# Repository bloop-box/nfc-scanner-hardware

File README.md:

# Bloop NFC Scanner Hardware

[Documentation](https://bloop-box.github.io/nfc-scanner-hardware)

Connect an RC522 based NFC-Reader to your computer using USB

The project is based around a Raspberry Pi [RP2040](https://www.raspberrypi.com/documentation/microcontrollers/rp2040.html) microcontroller. It would have been possible to solve this with a much simpler controller but availability and pricing at the time of development as well as ease of use made the RP2040 with built in USB the best choice. 

The board is designed using KiCAD 6 with production and assembly by JLCPCB in mind. All parts are selected to be available from JLCPCB at the time of writing and as many parts as possible are used from their basic library.

## Case
A simple case design can be found in the case subfolder. It fits when the two boards are connected with standard angled 2.54mm pitch connectors as seen in the picture. 

The two halves can be connected with self-tapping, countersunk M3x6 screws

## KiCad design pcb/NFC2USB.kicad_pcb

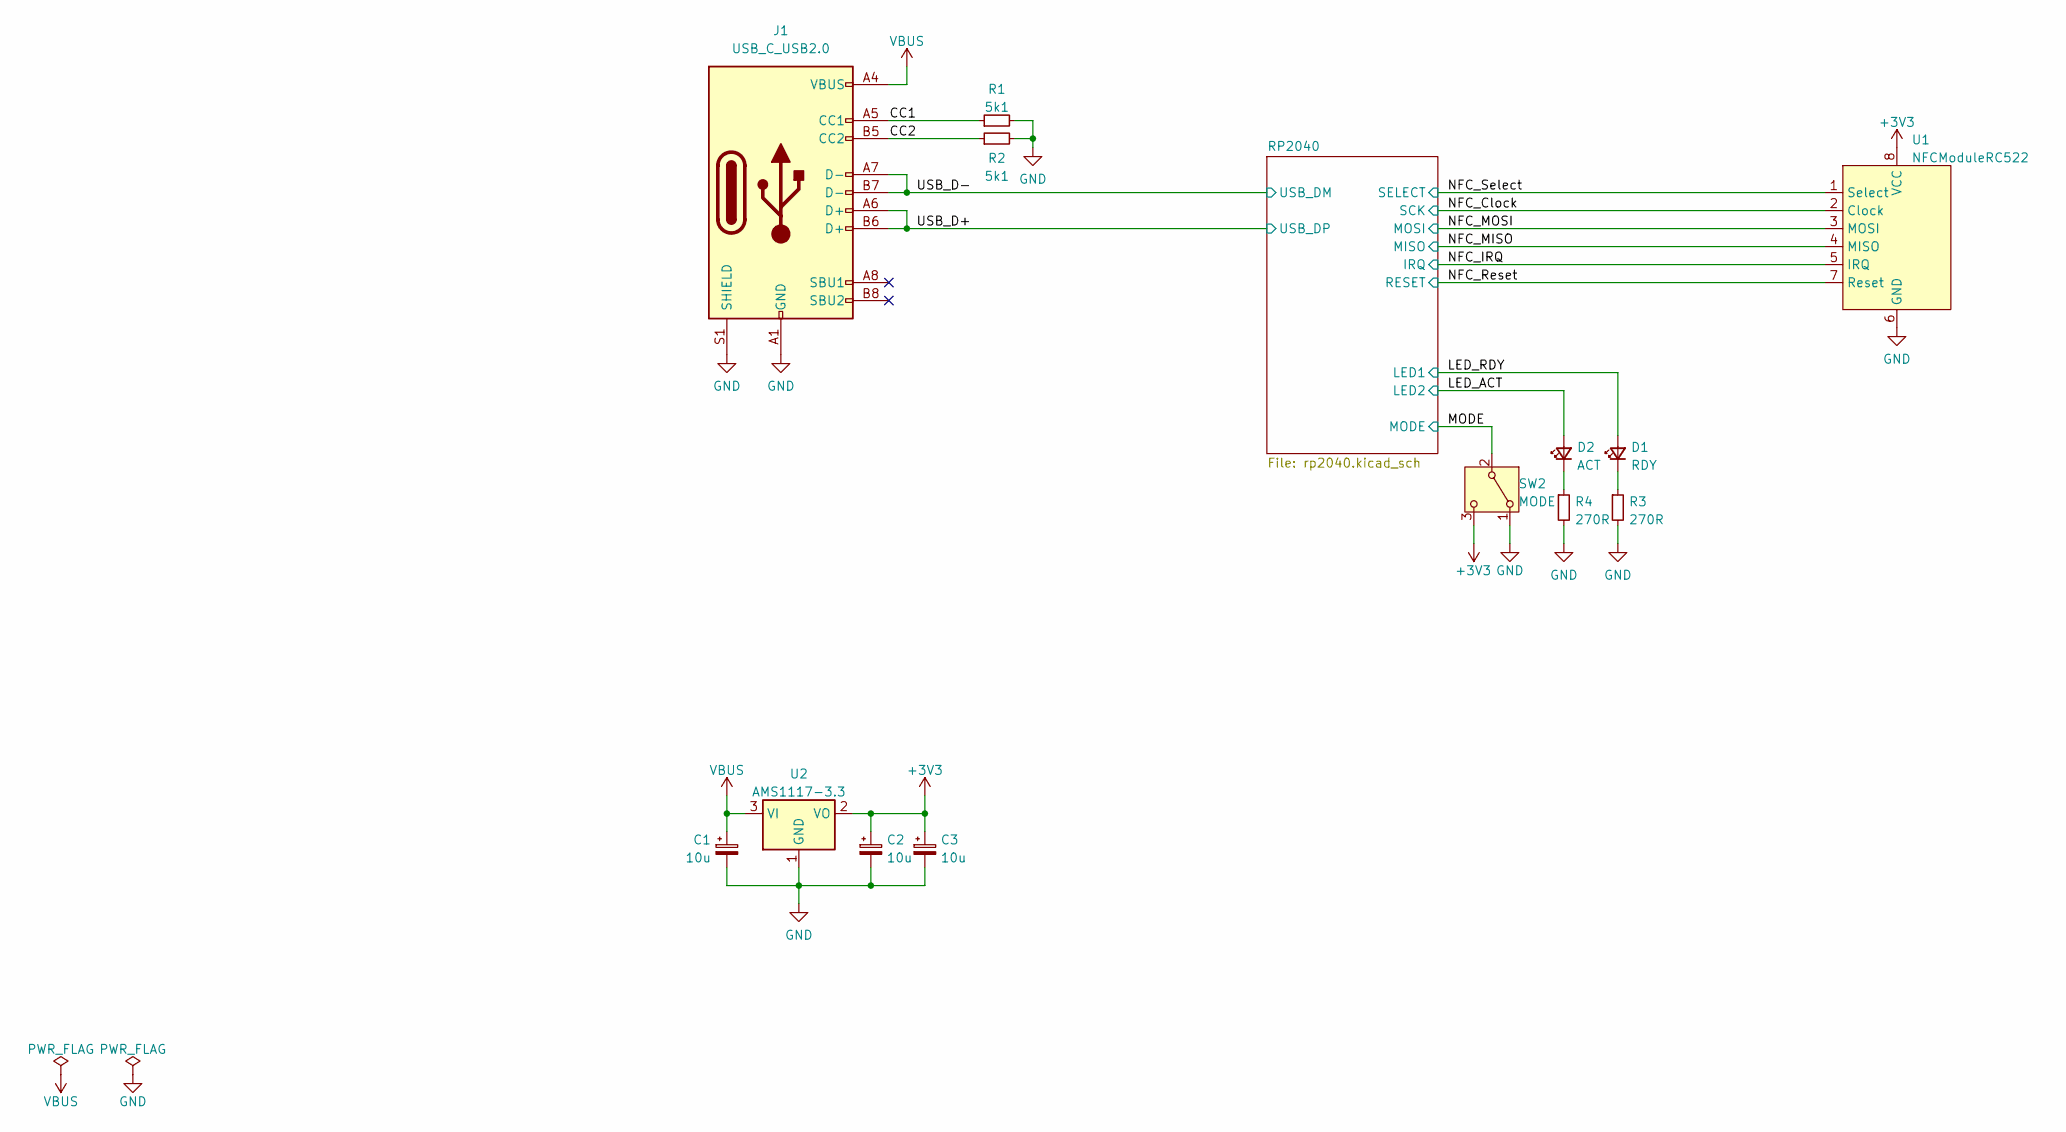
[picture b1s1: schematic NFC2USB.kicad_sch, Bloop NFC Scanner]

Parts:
C1, C2, C3: 10u; CP_EIA-3216-18_Kemet-A; LCSC C7171
D1: RDY; LED_0603_1608Metric; LCSC C72038
D2: ACT; LED_0603_1608Metric; LCSC C72043
J1: USB_C_USB2.0; USB_C_Receptacle_HRO_TYPE-C-31-M-12; LCSC C2894897
R1, R2: 5k1; R_0402_1005Metric; LCSC C25905
R3, R4: 270R; R_0603_1608Metric; LCSC C22966
SW2: MODE; SW_SPDT_PCM12; LCSC C431541
U1: NFCModuleRC522; PinSocket_1x08_P2.54mm_Vertical; LCSC C2897390
U2: AMS1117-3.3; SOT-223-3_TabPin2; LCSC C6186

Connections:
+3V3: C2.1, C3.1, SW2.3 (C), U1.8 (VCC), U2.2 (VO); also elsewhere on the board
/CC1: J1.A5 (CC1), R1.1
/CC2: J1.B5 (CC2), R2.1
/LED_ACT: D2.2 (A); also elsewhere on the board
/LED_RDY: D1.2 (A); also elsewhere on the board
/MODE: SW2.2 (B); also elsewhere on the board
/NFC_Clock: U1.2 (Clock); also elsewhere on the board
/NFC_IRQ: U1.5 (IRQ); also elsewhere on the board
/NFC_MISO: U1.4 (MISO); also elsewhere on the board
/NFC_MOSI: U1.3 (MOSI); also elsewhere on the board
/NFC_Reset: U1.7 (Reset); also elsewhere on the board
/NFC_Select: U1.1 (Select); also elsewhere on the board
/USB_D+: J1.A6 (D+), J1.B6 (D+); also elsewhere on the board
/USB_D-: J1.A7 (D-), J1.B7 (D-); also elsewhere on the board
GND: C1.2, C2.2, C3.2, J1.A1 (GND), J1.A12 (GND), J1.B1 (GND), J1.B12 (GND), J1.S1 (SHIELD), R1.2, R2.2, R3.2, R4.2, SW2.1 (A), U1.6 (GND), U2.1 (GND); also elsewhere on the board
unnamed: D1.1 (K), R3.1
unnamed: D2.1 (K), R4.1
VBUS: C1.1, J1.A4 (VBUS), J1.A9 (VBUS), J1.B4 (VBUS), J1.B9 (VBUS), U2.3 (VI)

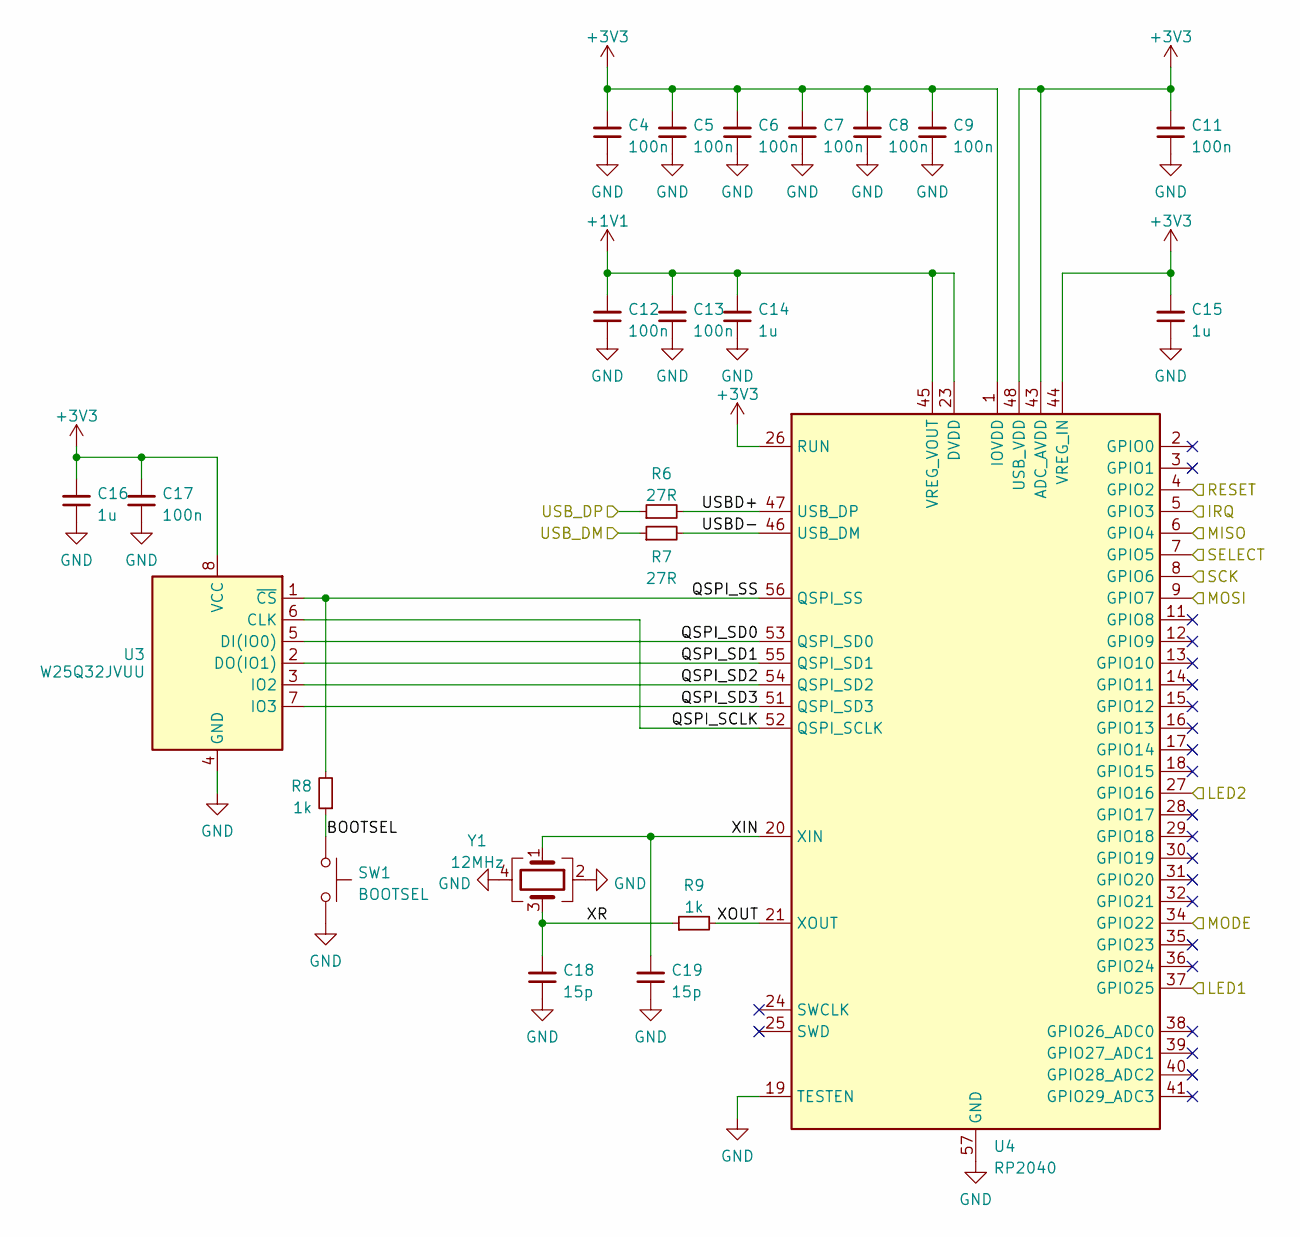
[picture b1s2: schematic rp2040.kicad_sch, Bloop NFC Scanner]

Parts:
C4, C5, C6, C7, C8, C9, C11, C12, C13, C17: 100n; C_0402_1005Metric; LCSC C1525
C14, C15, C16: 1u; C_0402_1005Metric; LCSC C52923
C18, C19: 15p; C_0402_1005Metric; LCSC C1548
R6, R7: 27R; R_0402_1005Metric; LCSC C25100
R8, R9: 1k; R_0402_1005Metric; LCSC C11702
SW1: BOOTSEL; SW_SPST_TL3342; LCSC C318884
U3: W25Q32JVUU; USON8 (3x4); LCSC C2999380
U4: RP2040; QFN-56-1EP_7x7mm_P0.4mm_EP3.2x3.2mm; LCSC C2040
Y1: 12MHz; Crystal_SMD_3225-4Pin_3.2x2.5mm; LCSC C9002

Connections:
+1V1: C12.2, C13.2, C14.2, U4.23 (DVDD), U4.45 (VREG_VOUT), U4.50 (DVDD)
+3V3: C4.2, C5.2, C6.2, C7.2, C8.2, C9.2, C11.2, C15.2, C16.2, C17.2, U3.8 (VCC), U4.1 (IOVDD), U4.10 (IOVDD), U4.22 (IOVDD), U4.26 (RUN), U4.33 (IOVDD), U4.42 (IOVDD), U4.43 (ADC_AVDD), U4.44 (VREG_IN), U4.48 (USB_VDD), U4.49 (IOVDD); also elsewhere on the board
/LED_ACT: U4.27 (GPIO16); also elsewhere on the board
/LED_RDY: U4.37 (GPIO25); also elsewhere on the board
/MODE: U4.34 (GPIO22); also elsewhere on the board
/NFC_Clock: U4.8 (GPIO6); also elsewhere on the board
/NFC_IRQ: U4.5 (GPIO3); also elsewhere on the board
/NFC_MISO: U4.6 (GPIO4); also elsewhere on the board
/NFC_MOSI: U4.9 (GPIO7); also elsewhere on the board
/NFC_Reset: U4.4 (GPIO2); also elsewhere on the board
/NFC_Select: U4.7 (GPIO5); also elsewhere on the board
/RP2040/BOOTSEL: R8.1, SW1.1
/RP2040/QSPI_SCLK: U3.6 (CLK), U4.52 (QSPI_SCLK)
/RP2040/QSPI_SD0: U3.5 (DI(IO0)), U4.53 (QSPI_SD0)
/RP2040/QSPI_SD1: U3.2 (DO(IO1)), U4.55 (QSPI_SD1)
/RP2040/QSPI_SD2: U3.3 (IO2), U4.54 (QSPI_SD2)
/RP2040/QSPI_SD3: U3.7 (IO3), U4.51 (QSPI_SD3)
/RP2040/QSPI_SS: R8.2, U3.1 (~CS), U4.56 (QSPI_SS)
/RP2040/USBD+: R6.2, U4.47 (USB_DP)
/RP2040/USBD-: R7.2, U4.46 (USB_DM)
/RP2040/XIN: C19.2, U4.20 (XIN), Y1.1
/RP2040/XOUT: R9.2, U4.21 (XOUT)
/RP2040/XR: C18.2, R9.1, Y1.3
/USB_D+: R6.1; also elsewhere on the board
/USB_D-: R7.1; also elsewhere on the board
GND: C4.1, C5.1, C6.1, C7.1, C8.1, C9.1, C11.1, C12.1, C13.1, C14.1, C15.1, C16.1, C17.1, C18.1, C19.1, SW1.2, U3.4 (GND), U4.19 (TESTEN), U4.57 (GND), Y1.2, Y1.4; also elsewhere on the board

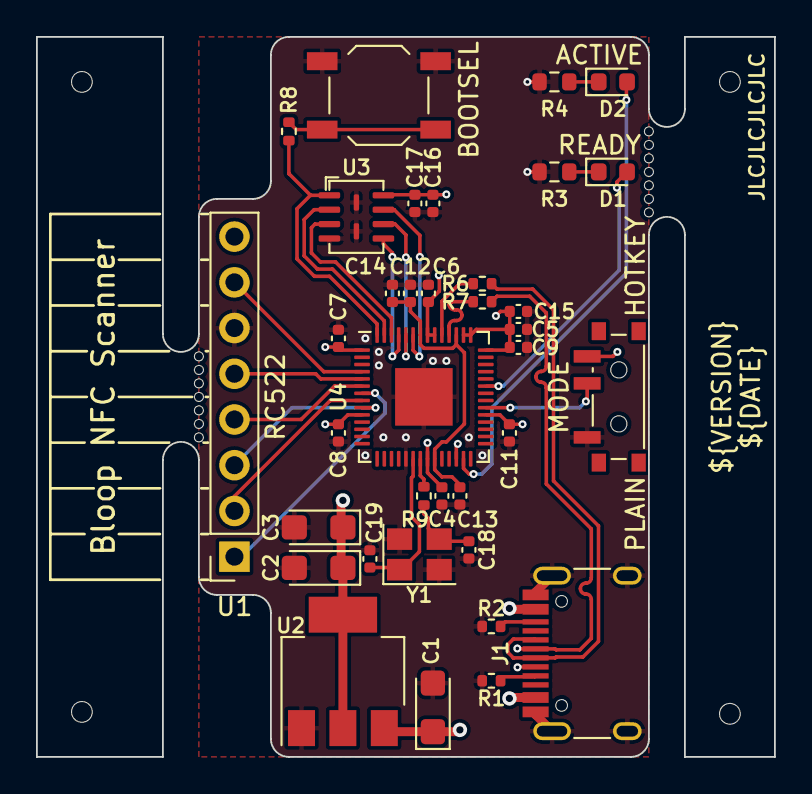
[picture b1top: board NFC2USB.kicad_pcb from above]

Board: 4 copper layers, 41.0 x 40.0 mm, 38 parts (0 on the bottom side), 31 nets.

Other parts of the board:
mouse-bite-2mm-slot, mouse-bite-2mm-slot#2: VAL**; mouse-bite-2x5mm-slot-onesided-v2

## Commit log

2023-04-16 feat: initial commit
2023-04-16 docs: update links
2023-04-16 style: symbol positioning
2023-04-16 feat: change flash footprint
2023-04-16 docs: update README title
2023-04-17 style: move LEDs
2023-04-17 chore(main): release 1.0.0
2023-04-17 style: update Titles
2023-05-02 feat: switch LED colors
    Switching the Activity and Ready LEDs for visibility reasons
2023-05-02 feat: add silkscreen to LEDs and switch
2023-05-03 fix: move mouse bites away from mode switch
2023-05-03 chore(main): release 1.1.0
2023-07-30 feat: add case
2023-10-01 fix: change mouse bites position, add silkscreen
    This commit includes the switch to KiCad 7 which is why there are so many unrelated changes in the files
    The mousebites were moved away from the mode switch
    Silkscreen text was added for mode switch and LEDs
2023-10-01 test: change violation severity
2023-10-01 fix: case design
    Fixing a few things noticed after getting a test print: widened the hole for the mode switch by 1mm in each direction, thickened the material over the LEDs to 0.5mm and tightened the screw holes by 0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
2023-12-07 docs: screws
2023-12-07 docs: update case picture
2024-08-19 chore: update to KiCad 8
2024-08-19 fix: add part number for connector
2024-08-19 chore(main): release 1.1.1
2024-08-19 docs: replace 3d model for connector
2024-08-29 ci: remove dependency between jobs
2025-07-14 fix: add 0.5mm to case height
    The latest RC522 modules have a different crystal which is slightly higher. This change makes the modules fit again.
2025-07-14 chore(main): release 1.1.2
